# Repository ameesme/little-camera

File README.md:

# Little Camera

A small black-and-white camera that posts to its own tiny blog, and everything around it.

```
firmware/    ESP32-S3 firmware (PlatformIO). Viewfinder, gallery, flash storage, BLE sync and update.
hardware/    The board it runs on: KiCad schematic + PCB, written by Python.
app/ios/     Bridge app (SwiftUI + CoreBluetooth). Carries photos off the camera and firmware back to it.
server/      Micro-blog + API (TypeScript, Hono, SQLite). One subdomain per owner.
  deploy/    Docker Compose + Caddy (wildcard TLS) for a VPS.
site/        The lttl.cam teaser, static on Vercel.
packages/    Shared TypeScript: PBM parsing, PNG encoding, short codes.
docs/        protocol.md (the contract), flows.md (who does what), mood.md (the camera as a small creature).
```

The service is `lttl.cam`, and a blog is one label under it (`mees.lttl.cam`). The landing page owns `lttl.cam/`, and everything the server answers on that domain sits under `/api` for machines or `/app` for people, so a proxy can tell the two apart.

Everything is black and white. Where a grey is unavoidable it is a 2 px checker.

## Step 0: back up the photos on your camera

Do this before you flash anything from here. It reads the flash and writes nothing:

```
cd firmware/tools/export
python3 -m venv .venv && .venv/bin/pip install -r requirements.txt
.venv/bin/python dump_flash.py --port /dev/cu.usbmodem*      # backup/<timestamp>/NNNN.pbm + .png
```

The partition table and file format are unchanged, so flashing keeps the photos on the device too, and the first sync uploads them all.

## Firmware

```
cd firmware
pio run -e v3q -t upload -t monitor
cd tools/preview && make scenes     # the UI without hardware, BMPs in out/
```

Read `firmware/AGENTS.md` before anything hardware-facing.

Press = shoot. Hold 0.7 s in the viewfinder = gallery (press = next, hold = back). On the review screen press = save, hold 1.5 s = trash. Asleep: hold 1 s to wake, a tap only chirps.

The camera has a mood (`docs/mood.md`): it sleeps with a smile after a photo, loses it over a week, and chirps for attention. The sounds are composed, not recorded, and `cd firmware/tools/chirp && make bands` renders them to WAV.

New firmware can also come over Bluetooth from the app (`docs/protocol.md` §3.7). It is written to the slot the camera is not running from, and the bootloader only points at it once every byte has arrived and the SHA-256 matches, so a failed update costs time and nothing else. `ota revert` on the USB console is the way back after you flash over the wire.

## Hardware

v3q, 62.8 × 42.82 mm, four layers, 80 parts, KiCad 10. Schematic `hardware/pcb/little_camera.kicad_sch`, board `hardware/pcb/little_camera.kicad_pcb`, and `little_camera_2d_view.svg` next to them if you have no KiCad. Neither is drawn by hand: `hardware/pcb/gen/design.py` holds every part and connection and the rest of `gen/` builds, places and routes from it. See `hardware/README.md`.

Pins are shared with the firmware and written down in `firmware/AGENTS.md`. Change them in both places.

## Server

```
pnpm install
pnpm dev      # http://localhost:3000/app, blogs at http://<handle>.localhost:3000
pnpm test
pnpm seed     # demo blog at http://mees.localhost:3000
```

Without SMTP settings every email lands in `/app/dev/mailbox`. `server/README.md` has the environment variables and the fake camera; `server/deploy/` has production, including how a firmware release is published.

## iOS app

```
cd app/ios && xcodegen generate && open LittleCamera.xcodeproj
```

Needs a real device, because Bluetooth. Set the server URL on first launch. The app never signs in: it identifies as the camera it is paired with.

## The whole flow

Make the blog in the app, confirm the address from the link it emails you, then photograph the QR the app draws and press send: the app uploads it, the server binds the camera to your blog, and every photo you send from then on lands on `https://<handle>.lttl.cam`. Friends join with their email and get one link per batch of new pictures. The web only ever shows pictures — everything else is the app. Step by step in `docs/flows.md`.

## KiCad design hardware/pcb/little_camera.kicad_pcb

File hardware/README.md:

# Little Camera — hardware

The board the firmware runs on. KiCad 10, four copper layers, 80 parts, 58 nets. Current revision **v3q**.

```
pcb/little_camera.kicad_sch     schematic
pcb/little_camera.kicad_pcb     board
pcb/little_camera_2d_view.svg   the board as a picture, no KiCad needed
pcb/gen/                        the Python that writes the board
pcb/fab/gerbers/                what was sent to the fab
pcb/out/*.md                    verification and audit records (the rest of out/ is generated)
```

The board is not drawn by hand. `pcb/gen/design.py` is the one place that holds the parts and every connection, `pcb/gen/v3build.py` cuts the bare frame and stackup, `pcb/gen/v3place.py` places, and routing goes out as a `.dsn` to freerouting and comes back as a `.ses` (`pcb/gen/route/`, not tracked). Open pcbnew and drag a track and the script and the board stop agreeing, so change the script and regenerate instead.

Pin assignments are the contract with the firmware. They live in `firmware/AGENTS.md` and have to change in both places at once.

Read before a respin: `pcb/out/verification_v3q.md` for what changed and why, with the checks taken before ordering, and `pcb/out/electrical_audit_2026-10-03.md` for the external review it answers.

## Next revision

Firmware works around all three on v3q; none can be fixed in firmware.

- **Shutter onto an RTC pad.** It is on IO44 (module pin 36), which cannot wake the S3 from deep sleep: only GPIO 0-21 can. So the camera can only light-sleep (~4 mA), and the deep sleep firmware does at a flat battery can only be woken by USB, through VBUS sense on IO16. **IO15 (module pin 8) is free** and an RTC pad; moving `SHUTTER` there keeps R26/C24 as they are and lets the button wake deep sleep, which is the largest power saving on this design. The pin table in `firmware/AGENTS.md` changes with it.
- **Replace U8, the panel's VCOM oscillator.** The 74LVC1G14 RC oscillator driving EXTCOMIN draws ~2 mA, measured by bridging C18: half of light sleep, and nearly all of deep sleep. The likely cause, not yet measured: the RC's slow edges hold the Schmitt input mid-rail, where a CMOS gate conducts straight through. Options, cheapest in current first: a nano-power timer (TPL5010-class, tens of nA) or a 32 kHz crystal oscillator with a divider, still on EXTCOMIN with EXTMODE high; or EXTCOMIN driven by an S3 RTC pin from the ULP, which keeps VCOM running through deep sleep for µA. Not EXTMODE low with software VCOM: deep sleep would then leave the panel on DC.
- **J5 battery polarity marking.** The `+` silkscreen fell off the board edge, and there is no reverse-polarity protection.

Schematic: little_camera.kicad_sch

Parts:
BZ1: MLT-5020; Buzzer_SMD_MLT5020
C1, C2: 4.7uF; C_0603_1608Metric
C3: 22uF; C_0805_2012Metric
C4, C8, C10, C12, C22, C23: 1uF; C_0402_1005Metric
C5: 10uF; C_0805_2012Metric
C6, C7, C14, C19, C20, C24: 100nF; C_0402_1005Metric
C9, C11, C13: 2.2uF; C_0603_1608Metric
C16, C17, C21: 10uF; C_0603_1608Metric
C18: 1uF; C_0603_1608Metric
D1: B5819W; D_SOD-123
D2: CHG; LED_0603_1608Metric
D3: CAM ON; LED_0603_1608Metric
D4: 1N4148WS; D_SOD-323
D5, D6: ESD9L5.0ST5G-N; D_DFN1006-2
FLG1, FLG2, FLG3, FLG5: PWR_FLAG
J1: USB-C; USB_C_ShouHan_TYPE-C-16P-CB0.8-073
J2: OV2640 DVP; FPC_BXCONN_FC-05B24P21H20
J3: LS027B7DH01; FPC_BXCONN_FC-05B10P21H20
J4: DOCK / I2C; TestPads_Dock3_P2.54
J5: BAT; BAT_Pads_Small
L1: 4.7uH; L_0805_2012Metric
Q1: AO3401A; SOT-23
Q2: DMG1012UW-7; SOT-323_SC-70
R1, R2, R5: 5.1k; R_0402_1005Metric
R3, R12, R28, R31: 100k; R_0402_1005Metric
R4, R34, R35: 1M; R_0402_1005Metric
R6, R27: 1k; R_0402_1005Metric
R7: 47k; R_0402_1005Metric
R8: 33k; R_0402_1005Metric
R9: 51k; R_0402_1005Metric
R10, R11, R15, R16: 4.7k; R_0402_1005Metric
R13, R14, R20, R21, R26: 10k; R_0402_1005Metric
R17: 2.2k; R_0402_1005Metric
R19, R33: 200k; R_0402_1005Metric
R22, R23, R24, R25: 330R; R_0402_1005Metric
SW1: D2MQ-1-TR; SW_Omron_D2MQ-1-TR
SW2: BOOT; SW_Pads_Short
SW3: RESET; SW_Pads_Short
U1: ESP32-S3-WROOM-1-N16R8; ESP32-S3-WROOM-1
U2: TP4054; SOT-23-5
U4: TLV75533PDQNR; LDO_X2SON-4_1x1_P0.65
U5: TLV75528PDQNR; LDO_X2SON-4_1x1_P0.65
U6: TLV75512PDQNR; LDO_X2SON-4_1x1_P0.65
U7: TPS61222; SOT-363_SC-70-6
U8: 74LVC1G14GW; SOT-353_SC-70-5
U10: AP2112K-3.3; SOT-23-5

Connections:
+3V3: BZ1.1 (+), C5.1, C19.1, C20.1, C21.1, C22.1, D4.1 (K), J4.3, R10.1, R11.1, R20.1, R21.1, R26.1, U1.2 (3V3), U8.5 (VCC), U10.5 (VOUT)
AVDD: C11.1, J2.4, U5.1 (OUT)
BOOT: R21.2, SW2.1, U1.27 (IO0)
BUZZ: R27.1, U1.16 (IO46)
BUZZ_DRV: BZ1.2 (-), D4.2 (A), Q2.3 (D)
BUZZ_G: Q2.1 (G), R27.2, R28.1
CAM_D0: J2.19, U1.32 (IO39)
CAM_D1: J2.21, U1.34 (IO41)
CAM_D2: J2.22, U1.35 (IO42)
CAM_D3: J2.20, U1.33 (IO40)
CAM_D4: J2.18, U1.31 (IO38)
CAM_D5: J2.16, U1.24 (IO47)
CAM_D6: J2.14, U1.23 (IO21)
CAM_D7: J2.12, U1.21 (IO13)
CAM_EN: R12.1, U1.26 (IO45), U4.3 (EN), U5.3 (EN), U6.3 (EN)
CAM_HREF: J2.9, U1.20 (IO12)
CAM_PCLK: J2.17, U1.25 (IO48)
CAM_PWDN: J2.8, R13.2, U1.19 (IO11)
CAM_RESET: C14.1, J2.6, R14.2, U1.17 (IO9)
CAM_SIOC: J2.5, R15.2, U1.12 (IO8)
CAM_SIOD: J2.3, R16.2, U1.11 (IO18)
CAM_VSYNC: J2.7, U1.18 (IO10)
CAM_XCLK: J2.13, U1.22 (IO14)
CC1: J1.A5 (CC1), R1.1
CC2: J1.B5 (CC2), R2.1
CHG_PROG: R5.1, U2.5 (PROG)
CHG_STAT: R31.2, R33.1, U1.10 (IO17)
CHG_STAT_OD: D2.1 (K), R7.2, R31.1, U2.1 (STAT)
DOVDD: C9.1, J2.11, R13.1, R14.1, R15.1, R16.1, R17.1, U4.1 (OUT)
DVDD: C13.1, J2.10, U6.1 (OUT)
EXTCOMIN: J3.4, R19.1, U8.4
GND: C1.2, C2.2, C3.2, C4.2, C5.2, C6.2, C7.2, C8.2, C9.2, C10.2, C11.2, C12.2, C13.2, C14.2, C16.2, C17.2, C18.2, C19.2, C20.2, C21.2, C22.2, C23.2, C24.2, D3.1 (K), D5.2 (A), D6.2 (A), FLG1.1, J1.A1 (GND), J1.A12 (GND), J1.B1 (GND), J1.B12 (GND), J1.SH (SHIELD), J2.2, J2.15, J3.9, J3.10, J4.1, J4.6, J5.2, Q2.2 (S), R1.2, R2.2, R4.2, R5.2, R9.2, R12.2, R28.2, R33.2, R35.2, SW1.2, SW2.2, SW3.2, U1.1 (GND), U1.40 (GND), U1.41 (GND), U2.2 (V_{SS}), U4.2 (GND), U4.5 (EP), U5.2 (GND), U5.5 (EP), U6.2 (GND), U6.5 (EP), U7.3 (GND), U8.3 (GND), U10.2 (GND)
LCD_DISP: R25.1, U1.7 (IO7)
LCD_DISP_P: J3.5, R25.2
LCD_SCLK: R22.1, U1.4 (IO4)
LCD_SCLK_P: J3.1, R22.2
LCD_SCS: R24.1, U1.6 (IO6)
LCD_SCS_P: J3.3, R24.2
LCD_SI: R23.1, U1.5 (IO5)
LCD_SI_P: J3.2, R23.2
LED_CAM: D3.2 (A), R17.2
LED_CHG: D2.2 (A), R6.2
MCU_EN: C23.1, R20.2, SW3.1, U1.3 (EN)
OSC_RC: C18.1, R19.2, U8.2
PFET_GATE: Q1.1 (G), R3.2, R4.1
SCL_SYS: J4.5, R11.2, U1.38 (IO2)
SDA_SYS: J4.4, R10.2, U1.39 (IO1)
SHUTTER: C24.1, R26.2, SW1.1, U1.36 (RXD0)
SPARE_1: J4.2, U1.37 (TXD0)
SW_L: FLG5.1, L1.2, U7.5 (L)
USB_DM: D6.1 (K), J1.A7 (D-), J1.B7 (D-), U1.13 (USB_D-)
USB_DP: D5.1 (K), J1.A6 (D+), J1.B6 (D+), U1.14 (USB_D+)
VBAT: C2.1, C16.1, J5.1, L1.1, Q1.3 (D), R34.1, U2.3 (V_{BAT}), U7.1 (VIN), U7.6 (EN)
VBAT_ADC: C7.1, R34.2, R35.1, U1.15 (IO3)
VBUS: C1.1, D1.2 (A), FLG2.1, J1.A4 (VBUS), J1.A9 (VBUS), J1.B4 (VBUS), J1.B9 (VBUS), R3.1, R6.1, R7.1, R8.1, U2.4 (V_{DD})
VBUS_SENSE: C6.1, R8.2, R9.1, U1.9 (IO16)
VDISP: C17.1, J3.6, J3.7, J3.8, U7.2 (FB), U7.4 (VOUT)
VSYS: C3.1, C4.1, C8.1, C10.1, C12.1, D1.1 (K), FLG3.1, Q1.2 (S), U4.4 (IN), U5.4 (IN), U6.4 (IN), U10.1 (VIN), U10.3 (EN)

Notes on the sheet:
USB-C input
power path, charger, 3V3
battery sense + system I2C
camera rails + DVP connector
Sharp panel, 5V boost, hardware VCOM
shutter, buzzer, spare IO
ESP32-S3 support
ESP32-S3-WROOM-1-N16R8

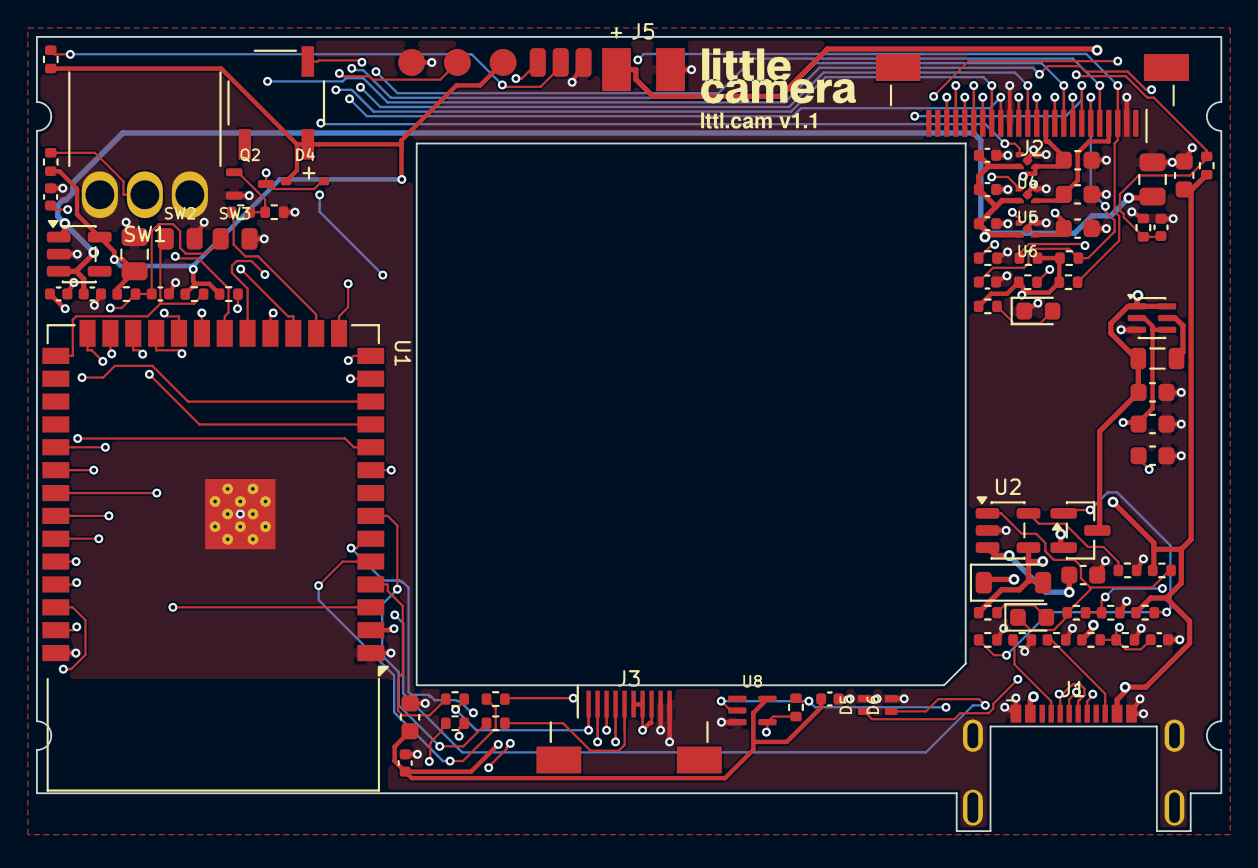
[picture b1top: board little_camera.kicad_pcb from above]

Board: 4 copper layers, 65.8 x 44.1 mm, 83 parts (0 on the bottom side), 58 nets.

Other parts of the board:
MECH1: LS027B7DH01 panel; MECH_LS027B7DH01
MECH2: LP403030 cell; MECH_LP552035
MECH3: OV2640 module (mock-up); MECH_OV2640_CAM

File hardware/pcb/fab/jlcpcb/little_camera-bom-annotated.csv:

Comment,Designator,Footprint,JLCPCB Part #,Qty,MPN,Library,Stock,Note
100k,"R3,R12,R28,R31",Resistor_SMD:R_0402_1005Metric,C25741,4,0402WGF1003TCE,basic,9158565,
100nF,"C6,C7,C14,C19,C20,C24",Capacitor_SMD:C_0402_1005Metric,C1525,6,CL05B104KO5NNNC,basic,23056837,0402 16V X7R
10k,"R13,R14,R20,R21,R26",Resistor_SMD:R_0402_1005Metric,C25744,5,0402WGF1002TCE,basic,22360849,
1M,"R4,R34,R35",Resistor_SMD:R_0402_1005Metric,C26083,3,0402WGF1004TCE,basic,2548709,
1k,"R6,R27",Resistor_SMD:R_0402_1005Metric,C11702,2,0402WGF1001TCE,basic,8133473,
1uF,"C4,C8,C10,C12,C22,C23",Capacitor_SMD:C_0402_1005Metric,C52923,6,CL05A105KA5NQNC,basic,5951968,0402 25V X5R
2.2k,R17,Resistor_SMD:R_0402_1005Metric,C25879,1,0402WGF2201TCE,basic,2354371,
200k,"R19,R33",Resistor_SMD:R_0402_1005Metric,C25764,2,0402WGF2003TCE,basic,2347635,"R33 STAT divider, R19 VCOM oscillator (v3q)"
330R,"R22,R23,R24,R25",Resistor_SMD:R_0402_1005Metric,C25104,4,0402WGF3300TCE,basic,1251008,
33k,R8,Resistor_SMD:R_0402_1005Metric,C25779,1,0402WGF3302TCE,basic,1208545,v3q: VBUS divider top
4.7k,"R10,R11,R15,R16",Resistor_SMD:R_0402_1005Metric,C25900,4,0402WGF4701TCE,basic,15730046,
47k,R7,Resistor_SMD:R_0402_1005Metric,C25792,1,0402WGF4702TCE,basic,5630304,
5.1k,"R1,R2,R5",Resistor_SMD:R_0402_1005Metric,C25905,3,0402WGF5101TCE,basic,6263741,USB-C CC pull-downs; R5 TP4054 charge current (196mA)
51k,R9,Resistor_SMD:R_0402_1005Metric,C25794,1,0402WGF5102TCE,basic,1911293,v3q: VBUS divider bottom
10uF,"C16,C17,C21",Capacitor_SMD:C_0603_1608Metric,C96446,3,CL10A106MA8NRNC,basic,3424489,0603 25V X5R - chosen over the 10V basic part because C16/C17 sit on the 5V boost rail
1uF,C18,Capacitor_SMD:C_0603_1608Metric,C15849,1,CL10A105KB8NNNC,basic,6433783,0603 50V X5R - VCOM oscillator timing cap
2.2uF,"C9,C11,C13",Capacitor_SMD:C_0603_1608Metric,C23630,3,CL10A225KO8NNNC,basic,2652212,0603 16V X5R
4.7uF,"C1,C2",Capacitor_SMD:C_0603_1608Metric,C19666,2,CL10A475KO8NNNC,basic,2622319,0603 16V X5R
CHG/CAM ON,"D2,D3",LED_SMD:LED_0603_1608Metric,C2286,2,KT-0603R,basic,3789423,red
10uF,C5,Capacitor_SMD:C_0805_2012Metric,C15850,1,CL21A106KAYNNNE,basic,5193619,0805 25V X5R
22uF,C3,Capacitor_SMD:C_0805_2012Metric,C45783,1,CL21A226MAQNNNE,basic,4115394,0805 25V X5R
4.7uH,L1,Inductor_SMD:L_0805_2012Metric,C63166,1,MPL2012S4R7MHT,extended,105458,"Sunlord 0805, 800mA, 250mOhm"
MLT-5020,BZ1,lc:Buzzer_SMD_MLT5020,C94598,1,MLT-5020,extended,28936,footprint replaced to match
ESD9L5.0ST5G-N,"D5,D6",lc:D_DFN1006-2,C316041,2,ESD9L5.0ST5G-N,extended,405063,"v3q: BORN DFN1006-2 USB ESD, 0.6pF, pad 1 = cathode"
B5819W,D1,Diode_SMD:D_SOD-123,C8598,1,B5819W SL,basic,544688,Changjing; Basic (was MDD Extended)
1N4148WS,D4,Diode_SMD:D_SOD-323,C2128,1,1N4148WS,basic,2267959,Changjing SOD-323
ESP32-S3-WROOM-1-N16R8,U1,lc:ESP32-S3-WROOM-1,C2913202,1,ESP32-S3-WROOM-1-N16R8,extended,21303,STANDARD-ONLY: forces JLCPCB Standard PCBA
LS027B7DH01,J3,lc:FPC_BXCONN_FC-05B10P21H20,C23398812,1,FC-05B10P21H20,extended,2313,"BXCONN, double-sided contacts, gold; FH12-10S drop-in ($0.14 vs $0.51)"
OV2640 DVP,J2,lc:FPC_BXCONN_FC-05B24P21H20,C23398820,1,FC-05B24P21H20,extended,4147,"BXCONN, double-sided contacts, gold; FH12-24S drop-in ($0.10 vs $0.51). Footprint pads in physical FH12 order"
TLV75512PDQNR,U6,lc:LDO_X2SON-4_1x1_P0.65,C2867150,1,TLV75512PDQNR,extended,56,"TI X2SON-4 1x1, DVDD 1.2V; low stock - TECH PUBLIC TPTLV75512PDQNR C55191435 is pin-compatible"
TLV75528PDQNR,U5,lc:LDO_X2SON-4_1x1_P0.65,C2865384,1,TLV75528PDQNR,extended,72,"TI X2SON-4 1x1, AVDD 2.8V; low stock - TECH PUBLIC TPTLV75528PDQNR C55191439 is pin-compatible"
TLV75533PDQNR,U4,lc:LDO_X2SON-4_1x1_P0.65,C2861882,1,TLV75533PDQNR,extended,2078,"TI X2SON-4 1x1, DOVDD 3.3V"
AO3401A,Q1,Package_TO_SOT_SMD:SOT-23,C15127,1,AO3401A,basic,813323,Alpha & Omega; Basic P-FET (was SI2301 Extended)
AP2112K-3.3,U10,Package_TO_SOT_SMD:SOT-23-5,C51118,1,AP2112K-3.3TRG1,extended,40520,Diodes Inc.
TP4054,U2,Package_TO_SOT_SMD:SOT-23-5,C668215,1,TP4054,extended,145104,UMW; pin-compatible with MCP73831 (was $0.63)
DMG1012UW-7,Q2,Package_TO_SOT_SMD:SOT-323_SC-70,C156390,1,DMG1012UW-7,extended,2465,"v3q: Diodes SOT-323 N-FET, Vgs(th) <=1.0V, buzzer driver"
74LVC1G14GW,U8,Package_TO_SOT_SMD:SOT-353_SC-70-5,C19829653,1,74LVC1G14GW,extended,3364,TECH PUBLIC SC-70-5 (SOT-353)
TPS61222,U7,Package_TO_SOT_SMD:SOT-363_SC-70-6,C116461,1,TPS61222DCKR,extended,1082,
USB-C,J1,lc:USB_C_ShouHan_TYPE-C-16P-CB0.8-073,C2906289,1,TYPE-C 16P CB0.8 073,extended,30919,"SHOU HAN; mid-mount for 0.8 mm boards, STANDARD-ONLY; shell legs are plated slots (hand-soldered THT)"

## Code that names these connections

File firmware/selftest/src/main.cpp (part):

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
// ------------------------------------------------------------------ pins --
// Sharp LS027B7DH01 on J3, each line through a 330R guard.
constexpr int PIN_LCD_SCLK = 4;
constexpr int PIN_LCD_SI   = 5;
constexpr int PIN_LCD_SCS  = 6;   // active HIGH
constexpr int PIN_LCD_DISP = 7;   // HIGH = show
// VCOM comes from U8 (EXTCOMIN, ~6 Hz) with EXTMODE tied high, so the panel
// ignores the serial VCOM bit. The test toggles it anyway: free, and it keeps
// the panel safe if EXTMODE turns out not to be high on a real board.

constexpr int PIN_SHUTTER  = 44;  // D2MQ NO to GND, R26 10k pull-up, C24 100n: pressed = LOW
constexpr int PIN_BUZZ     = 46;  // Q2 gate (low-side FET, buzzer to +3V3). Must idle LOW.
constexpr int PIN_VBUS     = 16;  // VBUS * 51/84 (R8 33k / R9 51k): a logic input. At 5.0-5.2 V
                                  // USB it sits at 3.0-3.2 V, the top of the ADC range, so reading
                                  // it as a voltage only gives a saturated number.
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// GPIO43 (dock pad 2, flash fob trigger, U0TXD) is left alone: it idles high.

// Camera (J2, OV2640 DVP). CAM_Dn = Y(n+2), so CAM_D0 is the driver's d0.
constexpr int PIN_CAM_EN    = 45; // U4/U5/U6 enable, R12 pull-down
constexpr int PIN_CAM_PWDN  = 11;
constexpr int PIN_CAM_RESET = 9;
constexpr int PIN_CAM_XCLK  = 14;
constexpr int PIN_CAM_SIOD  = 18;
constexpr int PIN_CAM_SIOC  = 8;
constexpr int PIN_CAM_VSYNC = 10;
constexpr int PIN_CAM_HREF  = 12;
constexpr int PIN_CAM_PCLK  = 48;
constexpr int PIN_CAM_D[8]  = {39, 41, 42, 40, 38, 47, 21, 13};

// ------------------------------------------------------------- display --
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static uint32_t clockHz = 8000000;      // the app's proven speed; `s` toggles 2 MHz

static void begin() {
    pinMode(PIN_LCD_SCS, OUTPUT);
    digitalWrite(PIN_LCD_SCS, LOW);
    pinMode(PIN_LCD_DISP, OUTPUT);
    digitalWrite(PIN_LCD_DISP, HIGH);
    spi = new SPIClass(HSPI);
    spi->begin(PIN_LCD_SCLK, -1, PIN_LCD_SI, -1);  // write-only panel, no MISO
}

static uint8_t cmd(uint8_t c) {
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
static void transact(void (*body)()) {
    spi->beginTransaction(SPISettings(clockHz, MSBFIRST, SPI_MODE0));
    digitalWrite(PIN_LCD_SCS, HIGH);
    delayMicroseconds(6);
    body();
    delayMicroseconds(2);
    digitalWrite(PIN_LCD_SCS, LOW);
    spi->endTransaction();
}

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    uint32_t half = 500000 / hz;
    uint32_t end = micros() + ms * 1000;
    while ((int32_t)(end - micros()) > 0) {
        digitalWrite(PIN_BUZZ, HIGH);
        delayMicroseconds(half);
        digitalWrite(PIN_BUZZ, LOW);
        delayMicroseconds(half);
    }
    digitalWrite(PIN_BUZZ, LOW);
}

static void buzzerTune() {
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
static void camPinsHighZ() {
    // After the driver is gone nothing should drive into the unpowered sensor.
    const int pins[] = {PIN_CAM_PWDN, PIN_CAM_RESET, PIN_CAM_XCLK, PIN_CAM_SIOD, PIN_CAM_SIOC,
                        PIN_CAM_VSYNC, PIN_CAM_HREF, PIN_CAM_PCLK};
    for (int p : pins) pinMode(p, INPUT);
    for (int p : PIN_CAM_D) pinMode(p, INPUT);
}
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static void camProbe() {
    Serial.println("[prb] --- camera bus probe ---");
    camPinsHighZ();
    digitalWrite(PIN_CAM_EN, LOW);
    delay(50);
    int offSda = digitalRead(PIN_CAM_SIOD), offScl = digitalRead(PIN_CAM_SIOC);
    digitalWrite(PIN_CAM_EN, HIGH);
    delay(30);
    int sda = digitalRead(PIN_CAM_SIOD), scl = digitalRead(PIN_CAM_SIOC);
    int pwdn = digitalRead(PIN_CAM_PWDN), rst = digitalRead(PIN_CAM_RESET);
    Serial.printf("[prb] rails off: SIOD %d SIOC %d | rails on: SIOD %d SIOC %d PWDN %d RESET %d (all 1 = DOVDD up)\n",
                  offSda, offScl, sda, scl, pwdn, rst);
    snprintf(probeLines[0], 48, "DOVDD pull-ups: SDA%d SCL%d PWDN%d RST%d", sda, scl, pwdn, rst);

    // Wake the sensor the way the driver does: PWDN low, RESET pulse, XCLK on.
    pinMode(PIN_CAM_PWDN, OUTPUT);  digitalWrite(PIN_CAM_PWDN, LOW);
    pinMode(PIN_CAM_RESET, OUTPUT); digitalWrite(PIN_CAM_RESET, LOW);
    bool xclk = ledcAttach(PIN_CAM_XCLK, 20000000, 1) && ledcWrite(PIN_CAM_XCLK, 1);
    delay(10);
    digitalWrite(PIN_CAM_RESET, HIGH);
    delay(30);

    Wire.begin(PIN_CAM_SIOD, PIN_CAM_SIOC, 100000);
    char found[24] = "";
    int nFound = 0;
    for (uint8_t a = 0x08; a < 0x78; a++) {
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            }
            return 0;
        };
        digitalWrite(PIN_CAM_PWDN, HIGH);
        delay(30);
        int a1 = anyone();
        digitalWrite(PIN_CAM_PWDN, LOW);
        delay(30);
        Wire.end();
        Wire.begin(PIN_CAM_SIOC, PIN_CAM_SIOD, 100000);     // swapped
        int a2 = anyone();
        Wire.end();
        Wire.begin(PIN_CAM_SIOD, PIN_CAM_SIOC, 10000);      // 10 kHz
        int a3 = anyone();
        Serial.printf("[prb] what-ifs: PWDN high -> %s | SDA/SCL swapped -> %s | 10 kHz -> %s\n",
                      a1 ? "ACK" : "nothing", a2 ? "ACK" : "nothing", a3 ? "ACK" : "nothing");
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    }

    Wire.end();
    ledcDetach(PIN_CAM_XCLK);
    camPinsHighZ();
    digitalWrite(PIN_CAM_EN, LOW);
    Serial.println("[prb] --- done, rails off ---");
}

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    railHold = !railHold;
    if (railHold) {
        camPinsHighZ();
        digitalWrite(PIN_CAM_EN, HIGH);
        delay(20);
        pinMode(PIN_CAM_PWDN, OUTPUT);  digitalWrite(PIN_CAM_PWDN, LOW);
        pinMode(PIN_CAM_RESET, OUTPUT); digitalWrite(PIN_CAM_RESET, HIGH);
        bool x = ledcAttach(PIN_CAM_XCLK, 20000000, 1) && ledcWrite(PIN_CAM_XCLK, 1);
        Serial.printf("[cam] rails ON and held, XCLK %s. Measure C9 3.3 V, C11 2.8 V, C13 1.2 V. `e` again = off\n", x ? "on" : "FAILED");
    } else {
        ledcDetach(PIN_CAM_XCLK);
        camPinsHighZ();
        digitalWrite(PIN_CAM_EN, LOW);
        Serial.println("[cam] rails off");
    }
}

static bool camStart() {
    if (camUp) return true;
    digitalWrite(PIN_CAM_EN, HIGH);
    delay(20);   // three LDOs up, then R14/C14 releases RESET after ~1 ms

    camera_config_t c = {};
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    c.ledc_timer = LEDC_TIMER_0;
    c.pin_d0 = PIN_CAM_D[0]; c.pin_d1 = PIN_CAM_D[1]; c.pin_d2 = PIN_CAM_D[2]; c.pin_d3 = PIN_CAM_D[3];
    c.pin_d4 = PIN_CAM_D[4]; c.pin_d5 = PIN_CAM_D[5]; c.pin_d6 = PIN_CAM_D[6]; c.pin_d7 = PIN_CAM_D[7];
    c.pin_xclk = PIN_CAM_XCLK;
    c.pin_pclk = PIN_CAM_PCLK;
    c.pin_vsync = PIN_CAM_VSYNC;
    c.pin_href = PIN_CAM_HREF;
    c.pin_sccb_sda = PIN_CAM_SIOD;
    c.pin_sccb_scl = PIN_CAM_SIOC;
    c.pin_pwdn = PIN_CAM_PWDN;
    c.pin_reset = PIN_CAM_RESET;
    c.xclk_freq_hz = 20000000;
    c.frame_size = FRAMESIZE_QVGA;
    c.pixel_format = PIXFORMAT_GRAYSCALE;
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    if (camErr != ESP_OK) {
        Serial.printf("[cam] init failed: 0x%x (%s)\n", camErr, esp_err_to_name(camErr));
        camPinsHighZ();
        digitalWrite(PIN_CAM_EN, LOW);
        camProbe();
        return false;
    }
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    if (!camUp) return;
    esp_camera_deinit();
    camPinsHighZ();
    digitalWrite(PIN_CAM_EN, LOW);
    camUp = false;
    Serial.println("[cam] down, rails off");
}
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}

// ---------------------------------------------------------------- button --
static bool pressedRaw() { return digitalRead(PIN_SHUTTER) == LOW; }

enum class Btn { None, Tap, Hold };
constexpr uint32_t HOLD_MS = 1000;
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    // Wait for release, or the LOW level would wake us immediately.
    while (pressedRaw()) delay(5);
    delay(50);
    Lcd::frame("4/5 SLEEPING", "press the shutter to wake");
    Lcd::text(8, 60, "light sleep... (USB serial may drop)");
    Lcd::flush();
    Serial.println("[slp] light sleep: wake on IO44 LOW or 10 s timer");
    Serial.flush();
    delay(20);
    gpio_wakeup_enable((gpio_num_t)PIN_SHUTTER, GPIO_INTR_LOW_LEVEL);
    esp_sleep_enable_gpio_wakeup();
    esp_sleep_enable_timer_wakeup(10ULL * 1000 * 1000);
    gpio_hold_en((gpio_num_t)PIN_BUZZ);      // keep Q2 off through sleep
    uint32_t t0 = millis();
    esp_light_sleep_start();
    gpio_hold_dis((gpio_num_t)PIN_BUZZ);
    gpio_wakeup_disable((gpio_num_t)PIN_SHUTTER);
    esp_sleep_disable_wakeup_source(ESP_SLEEP_WAKEUP_TIMER);
    esp_sleep_wakeup_cause_t c = esp_sleep_get_wakeup_cause();
    if (c == ESP_SLEEP_WAKEUP_GPIO) sleepWakes++; else if (c == ESP_SLEEP_WAKEUP_TIMER) sleepTimer++;
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    Serial.flush();
    delay(300);                                   // let the supply reading settle after the redraw
    esp_sleep_enable_timer_wakeup((uint64_t)SWEEP_STEP_S * 1000 * 1000);
    gpio_hold_en((gpio_num_t)PIN_BUZZ);
    esp_light_sleep_start();
    gpio_hold_dis((gpio_num_t)PIN_BUZZ);
    esp_sleep_disable_wakeup_source(ESP_SLEEP_WAKEUP_TIMER);
}

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    Serial.println("[swp] sleep power sweep: 4 light-sleep steps + deep sleep");
    camStop();
    camPinsHighZ();
    digitalWrite(PIN_CAM_EN, LOW);

    sweepScreen(1, "light sleep, as before");
    sweepLightSleep();
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    Serial.println("[swp] deep sleep, reboot follows");
    Serial.flush();
    delay(300);
    digitalWrite(PIN_BUZZ, LOW);
    gpio_hold_en((gpio_num_t)PIN_BUZZ);
    gpio_hold_en((gpio_num_t)PIN_LCD_DISP);
    gpio_hold_en((gpio_num_t)PIN_LCD_SCS);
    gpio_deep_sleep_hold_en();
    esp_sleep_enable_timer_wakeup((uint64_t)SWEEP_STEP_S * 1000 * 1000);
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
